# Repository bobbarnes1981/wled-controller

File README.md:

# wled-controller

A controller board for wled with the following features

* ESP32 DevKitC pin layout
* Relay switched LED supply
* 4 level shifted led outputs
* 2 buttons
* Indicator LEDs for 5v in, Relay and 5v out
* INMP441 Microphone module connection
* Mini automotive fuses

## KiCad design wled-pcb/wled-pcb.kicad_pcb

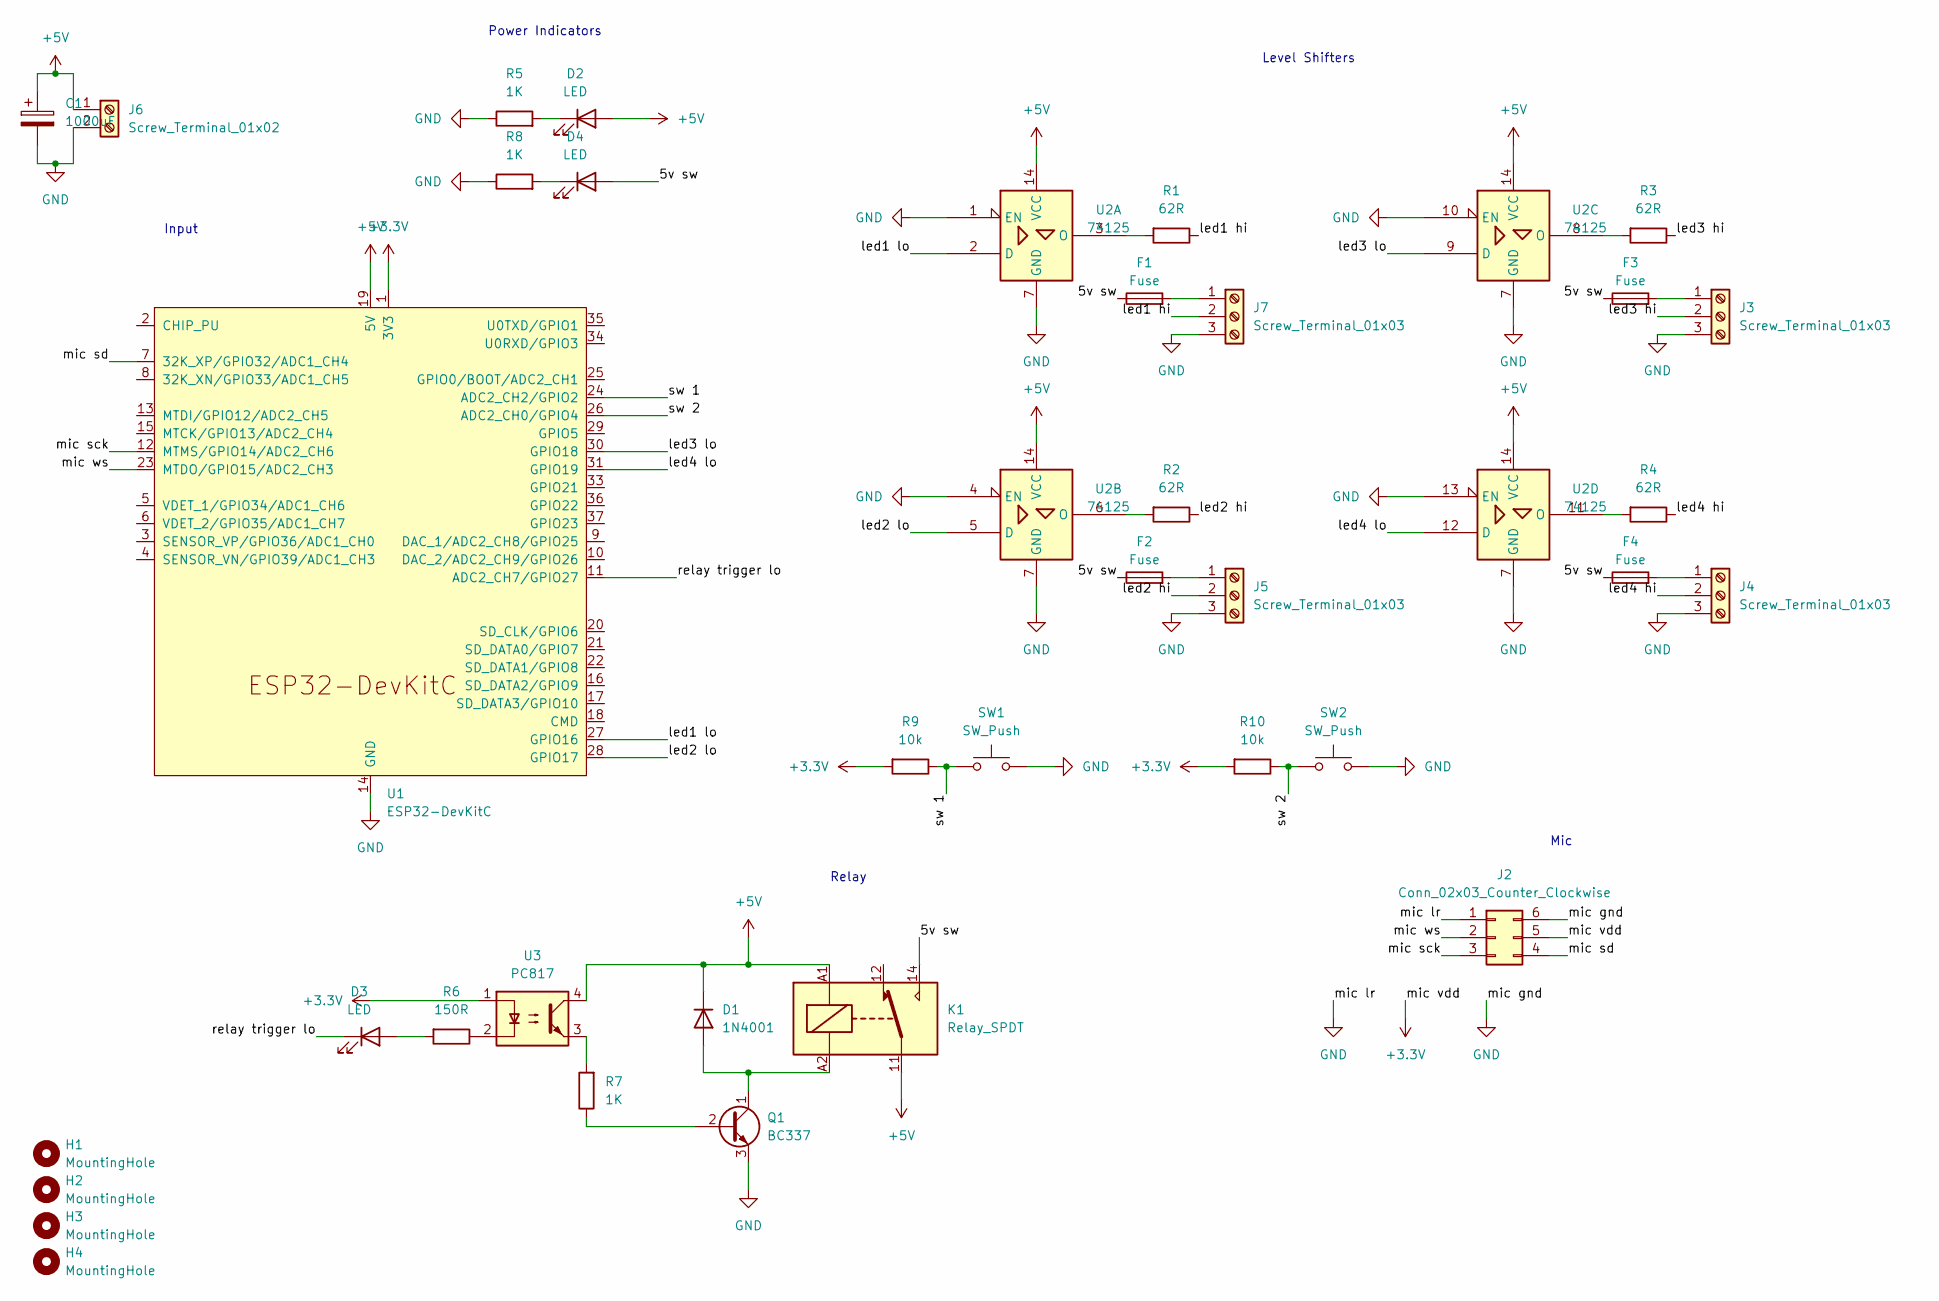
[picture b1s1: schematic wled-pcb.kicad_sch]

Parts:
C1: 1000uF; CP_Radial_D13.0mm_P5.00mm
D1: 1N4001; D_DO-41_SOD81_P10.16mm_Horizontal
D2, D3, D4: LED; LED_D5.0mm
F1, F2, F3, F4: Fuse; Fuseholder_Blade_Mini_Keystone_3568
H1, H2, H3, H4: MountingHole; MountingHole_3.2mm_M3_DIN965_Pad_TopBottom
J2: Conn_02x03_Counter_Clockwise; DIP-6_W7.62mm_LongPads
J3, J4, J5, J7: Screw_Terminal_01x03; TerminalBlock_bornier-3_P5.08mm
J6: Screw_Terminal_01x02; TerminalBlock_bornier-2_P5.08mm
K1: Relay_SPDT; Relay_SPDT_Omron_G2RL-1-E
Q1: BC337; TO-92_Inline
R1, R2, R3, R4: 62R; R_Axial_DIN0207_L6.3mm_D2.5mm_P10.16mm_Horizontal
R5, R7, R8: 1K; R_Axial_DIN0207_L6.3mm_D2.5mm_P10.16mm_Horizontal
R6: 150R; R_Axial_DIN0207_L6.3mm_D2.5mm_P10.16mm_Horizontal
R9, R10: 10k; R_Axial_DIN0207_L6.3mm_D2.5mm_P10.16mm_Horizontal
SW1, SW2: SW_Push; SW_PUSH-12mm_Wuerth-430476085716
U1: ESP32-DevKitC
U2: 74125; DIP-14_W7.62mm_LongPads
U3: PC817; DIP-4_W7.62mm

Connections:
+3.3V: J2.5, R9.2, R10.2, U1.1 (3V3), U3.1
+5V: C1.1, D1.1 (K), D2.2 (A), J6.1, K1.11, K1.A1, U1.19 (5V), U2.14 (VCC), U3.4
/5v sw: D4.2 (A), F1.1, F2.1, F3.1, F4.1, K1.14
/led1 hi: J7.2, R1.1
/led1 lo: U1.27 (GPIO16), U2.2 (D)
/led2 hi: J5.2, R2.1
/led2 lo: U1.28 (GPIO17), U2.5 (D)
/led3 hi: J3.2, R3.1
/led3 lo: U1.30 (GPIO18), U2.9 (D)
/led4 hi: J4.2, R4.1
/led4 lo: U1.31 (GPIO19), U2.12 (D)
/mic sck: J2.3, U1.12 (MTMS/GPIO14/ADC2_CH6)
/mic sd: J2.4, U1.7 (32K_XP/GPIO32/ADC1_CH4)
/mic ws: J2.2, U1.23 (MTDO/GPIO15/ADC2_CH3)
/relay trigger lo: D3.1 (K), U1.11 (ADC2_CH7/GPIO27)
/sw 1: R9.1, SW1.1, U1.24 (ADC2_CH2/GPIO2)
/sw 2: R10.1, SW2.1, U1.26 (ADC2_CH0/GPIO4)
GND: C1.2, J2.1, J2.6, J3.3, J4.3, J5.3, J6.2, J7.3, Q1.3 (E), R5.1, R8.1, SW1.2, SW2.2, U1.14 (GND), U1.32 (GND), U1.38 (GND), U2.1 (EN), U2.4 (EN), U2.7 (GND), U2.10 (EN), U2.13 (EN)
unnamed: D1.2 (A), K1.A2, Q1.1 (C)
unnamed: D2.1 (K), R5.2
unnamed: D3.2 (A), R6.2
unnamed: D4.1 (K), R8.2
unnamed: F3.2, J3.1
unnamed: F4.2, J4.1
unnamed: F2.2, J5.1
unnamed: F1.2, J7.1
unnamed: Q1.2 (B), R7.1
unnamed: R6.1, U3.2
unnamed: R7.2, U3.3
unnamed: R1.2, U2.3 (O)
unnamed: R2.2, U2.6 (O)
unnamed: R3.2, U2.8 (O)
unnamed: R4.2, U2.11 (O)

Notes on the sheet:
Relay
Level Shifters
Power Indicators
Input
Mic

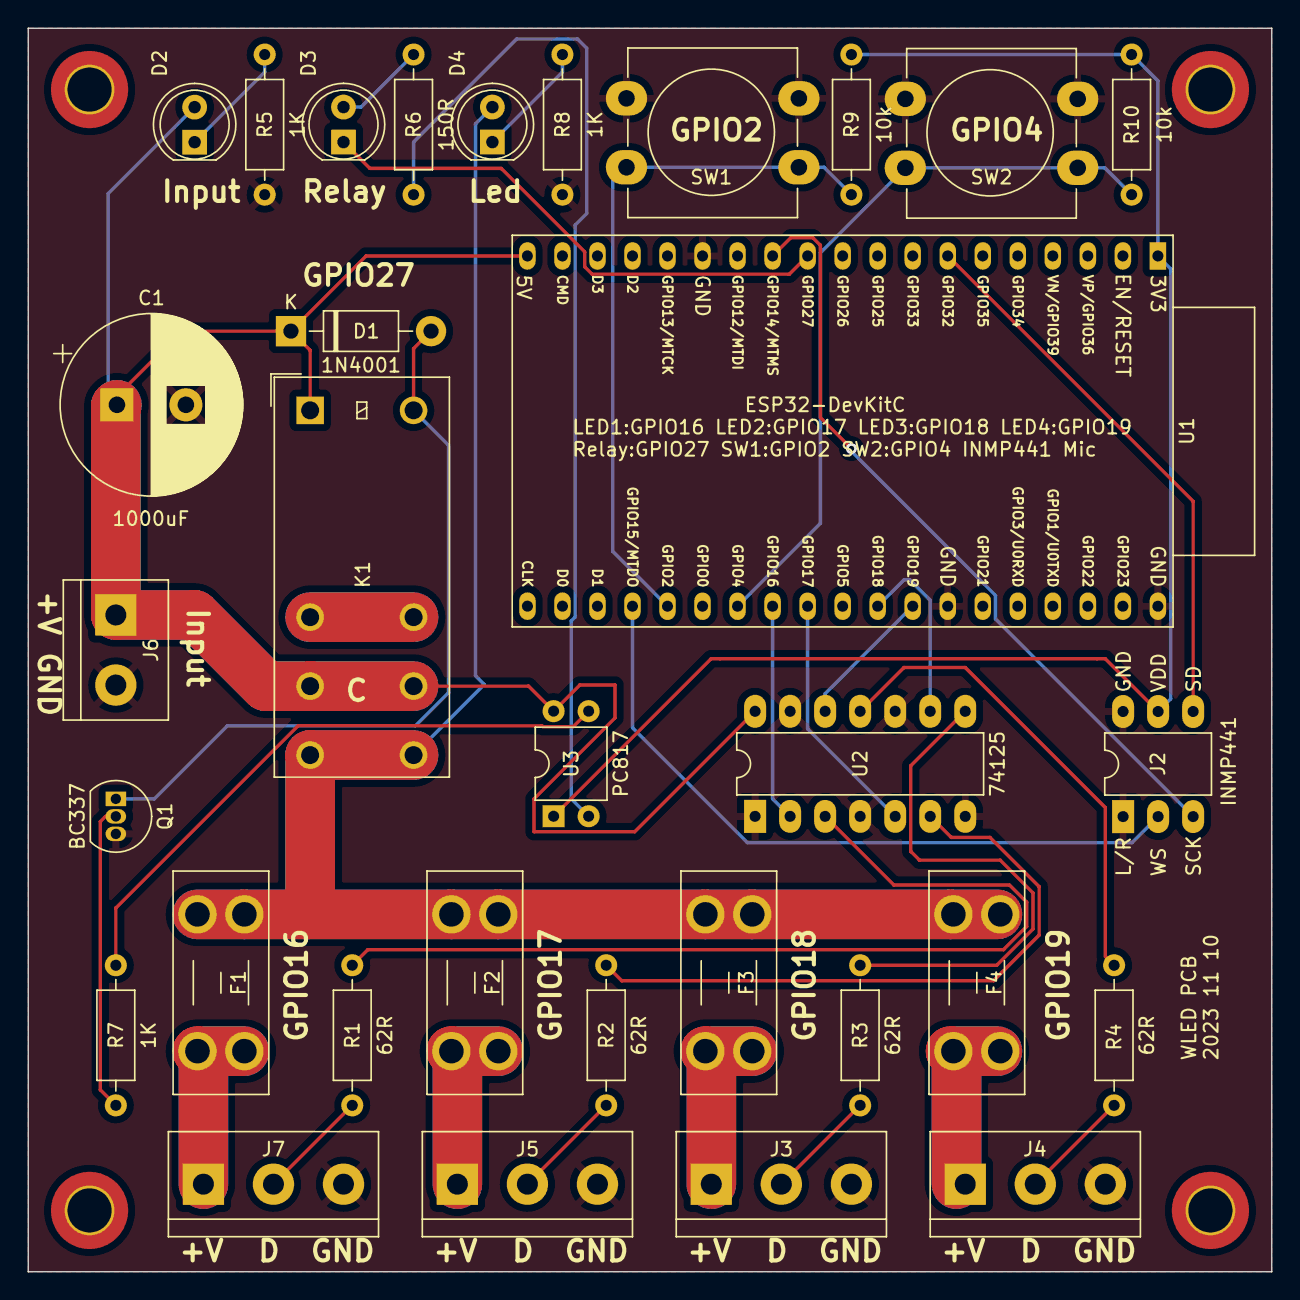
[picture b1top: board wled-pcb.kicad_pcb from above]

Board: 2 copper layers, 90.2 x 90.2 mm, 36 parts (0 on the bottom side), 33 nets.

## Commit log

2023-11-05 add footprints
2023-11-05 add footprints to pcb
2023-11-05 fix some mistakes, route some traces
2023-11-05 Add buttons, route tracks
2023-11-06 layout board smaller than 100x100
2023-11-06 route tracks
2023-11-06 generate gerbers
2023-11-06 remove gerbers
2023-11-06 use different pins for switches
2023-11-06 kicad plugin
2023-11-06 pcbway files
2023-11-06 3.6mm trace should give 6A@1oz and 10A@2oz
2023-11-10 Rotate spokes to pass DRC
2023-11-10 Add screenshots
2023-11-10 Duplicate power traces on both sides of PCB
2023-11-10 Add connector text
2023-11-13 Add more info to silkscreen
